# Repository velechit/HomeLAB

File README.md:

# HomeLAB
A miniature electronics lab (Oscilloscope + FuncGen + Breadboard + Arduino) for hobbyists

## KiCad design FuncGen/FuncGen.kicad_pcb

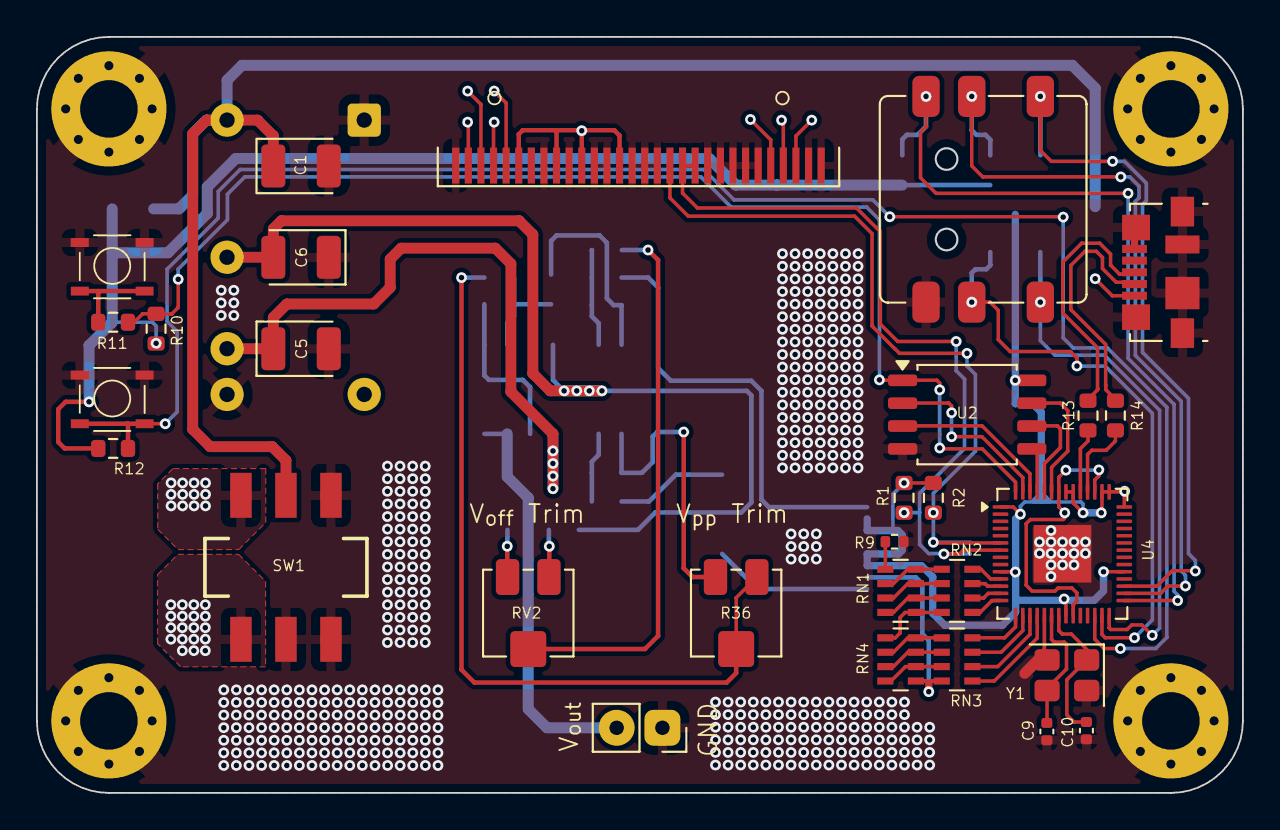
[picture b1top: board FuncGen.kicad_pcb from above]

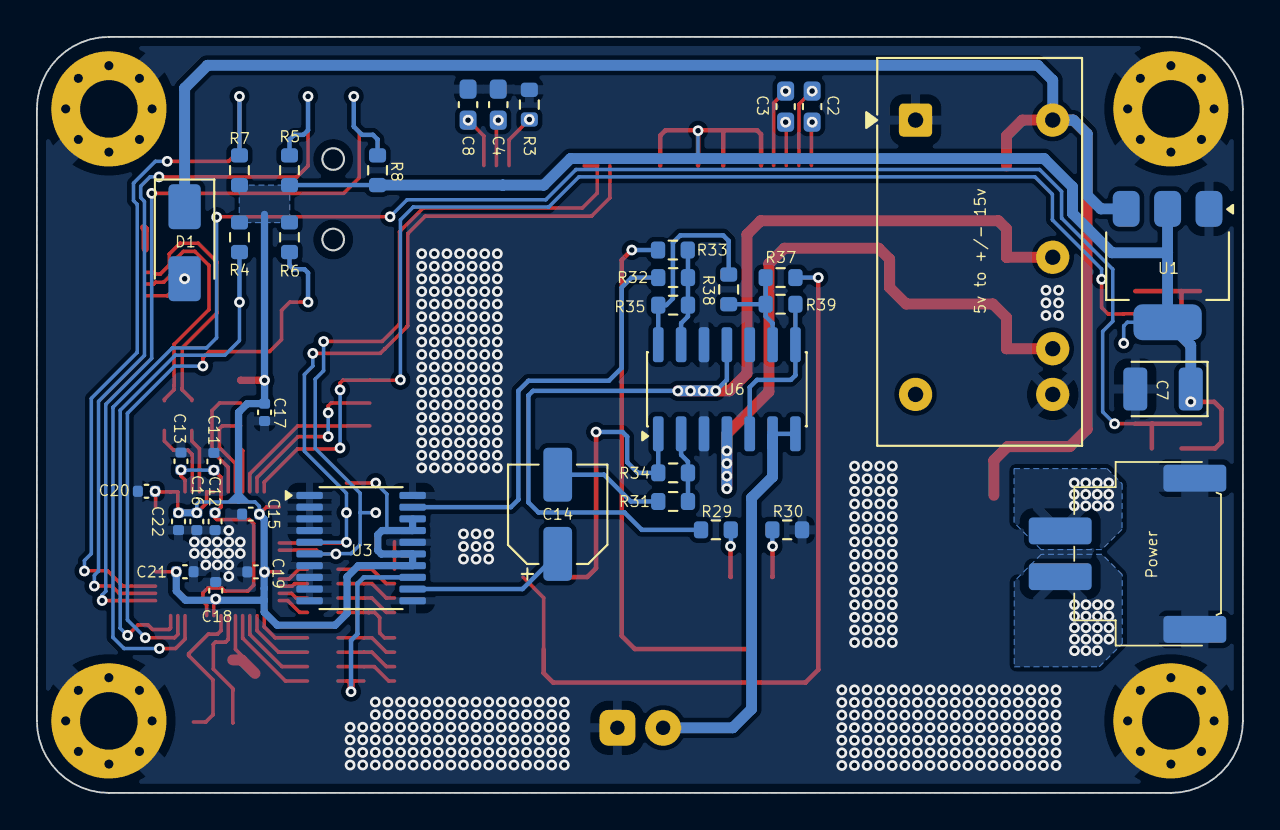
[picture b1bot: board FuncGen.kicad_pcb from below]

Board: 2 copper layers, 67.0 x 42.0 mm, 72 parts (39 on the bottom side), 68 nets.

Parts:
C1: 10u; CP_EIA-3528-21_Kemet-B
C2, C3: 1u; C_0603_1608Metric_Pad1.08x0.95mm_HandSolder
C4: 4.7u; C_0603_1608Metric_Pad1.08x0.95mm_HandSolder
C5, C6, C7: 4.7u; CP_EIA-3528-21_Kemet-B
C8: 2.2u; C_0603_1608Metric_Pad1.08x0.95mm_HandSolder
C9, C10: 22p; C_0402_1005Metric
C11, C12, C15, C16, C17, C18, C19, C20, C21: 100n; C_0402_1005Metric
C13, C22: 1u; C_0402_1005Metric
C14: 47u; CP_Elec_5x5.4
D1: SS34; D_SMA
DS1: 0.96" 128x64 OLED; OLED-128O064D
H1, H2, H3, H4: MountingHole_Pad; MountingHole_3.2mm_M3_Pad_Via
J1: PWR; batt-conn
J2: joystick-sleek
J3: USB_B_Micro; USB_Micro-B_Molex_47346-0001
J4: Conn_01x02; PinSocket_1x02_P2.54mm_Vertical
PS1: IA0515D; Converter_DCDC_XP_POWER-IAxxxxD_THT
R1, R2: 3.3k; R_0603_1608Metric
R3: 910k; R_0603_1608Metric
R4, R5, R6, R7, R8, R10, R12, R31: 10k; R_0603_1608Metric
R9: 10k; R_0402_1005Metric
R11, R30: 1k; R_0603_1608Metric
R13, R14: 27; R_0603_1608Metric
R29: 22k; R_0603_1608Metric
R32, R33, R38, R39: 100k; R_0603_1608Metric
R34, R37: 27k; R_0603_1608Metric
R35: 470k; R_0603_1608Metric
R36: 5k; Potentiometer_Bourns_3224J_Horizontal
RN1, RN4: 10k; R_Array_Concave_4x0603
RN2, RN3: 20k; R_Array_Concave_4x0603
RV2: 5k; Potentiometer_Bourns_3224J_Horizontal
SW1: PWR_SW; DPDT_SMT
SW2: BOOT; 4PINSW-MINI
SW3: RESET; 4PINSW-MINI
U1: LM1117; SOT-223-3_TabPin2
U2: W25Q32JVSS; SOIC-8_5.3x5.3mm_P1.27mm
U3: MCP4461-103; TSSOP-20_4.4x6.5mm_P0.65mm
U4: RP2040; QFN-56-1EP_7x7mm_P0.4mm_EP3.2x3.2mm
U6: TL074; SOIC-14_3.9x8.7mm_P1.27mm
Y1: 12MHz; Crystal_SMD_3225-4Pin_3.2x2.5mm

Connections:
+1V1: C11.2, C12.2, C13.2, U4.23 (DVDD), U4.45 (VREG_VOUT), U4.50 (DVDD)
+3V3: C7.1, C15.2, C16.2, C17.2, C18.2, C19.2, C20.2, C21.2, C22.2, DS1.6 (VBAT), DS1.9 (VDD), DS1.11 (BS1), DS1.14 (~RES), R1.1, R2.1, R4.1, R5.1, R6.1, R7.1, R8.1, R10.1, R12.1, U1.2 (VO), U2.8 (VCC), U3.14 (~WP), U3.15 (~RESET), U3.17 (VDD), U3.18 (P2B), U4.1 (IOVDD), U4.10 (IOVDD), U4.22 (IOVDD), U4.33 (IOVDD), U4.42 (IOVDD), U4.43 (ADC_AVDD), U4.44 (VREG_IN), U4.48 (USB_VDD), U4.49 (IOVDD)
+5V: C1.1, D1.1 (K), PS1.3 (+Vin), SW1.5 (B), U1.3 (VI)
+15V: C5.1, PS1.5 (+Vout), U6.4 (V+)
-15V: C6.2, PS1.4 (-Vout), R29.2, U6.11 (V-)
/BTN_DOWN: J2.D, R7.2, U4.31 (GPIO20)
/BTN_LEFT: J2.L, R6.2, U4.27 (GPIO16)
/BTN_MID: J2.M, R4.2, U4.28 (GPIO17)
/BTN_RIGHT: J2.R, R5.2, U4.30 (GPIO19)
/BTN_UP: J2.U, R8.2, U4.29 (GPIO18)
/DAC0: RN2.8 (R1.2), U4.11 (GPIO8)
/DAC1: RN2.7 (R2.2), U4.12 (GPIO9)
/DAC2: RN2.6 (R3.2), U4.13 (GPIO10)
/DAC3: RN2.5 (R4.2), U4.14 (GPIO11)
/DAC4: RN3.8 (R1.2), U4.15 (GPIO12)
/DAC5: RN3.7 (R2.2), U4.16 (GPIO13)
/DAC6: RN3.6 (R3.2), U4.17 (GPIO14)
/DAC7: RN3.5 (R4.2), U4.18 (GPIO15)
/QSPI_CLK: U2.6 (CLK), U4.52 (QSPI_SCLK)
/QSPI_SD0: U2.5 (DI/IO_{0}), U4.53 (QSPI_SD0)
/QSPI_SD1: U2.2 (DO/IO_{1}), U4.55 (QSPI_SD1)
/QSPI_SD2: U2.3 (~WP/IO_{2}), U4.54 (QSPI_SD2)
/QSPI_SD3: U2.7 (~HOLD/~RESET/IO_{3}), U4.51 (QSPI_SD3)
/QSPI_SS: R10.2, R11.1, U2.1 (~CS), U4.56 (QSPI_SS)
/SCL: DS1.18 (D0), R2.2, U3.5 (SCL), U4.6 (GPIO4)
/SDA: DS1.19 (D1), DS1.20 (D2), R1.2, U3.6 (SDA), U4.7 (GPIO5)
/USB.D+: J3.3 (D+), R13.1
/USB.D-: J3.2 (D-), R14.1
GND: C1.2, C4.1, C5.2, C6.1, C7.2, C8.1, C9.1, C10.1, C11.1, C12.1, C13.1, C15.1, C16.1, C17.1, C18.1, C19.1, C20.1, C21.1, C22.1, DS1.1 (GND), DS1.8 (VSS), DS1.10 (BS0), DS1.12 (BS2), DS1.13 (~CS), DS1.15 (D/~C), DS1.16 (R/~W), DS1.17 (E/~RD), DS1.21 (D3), DS1.22 (D4), DS1.23 (D5), DS1.24 (D6), DS1.25 (D7), DS1.29 (VLSS), DS1.30 (GND), H1.1, H2.1, H3.1, H4.1, J1.3, J2.COM, J3.5 (GND), J3.6 (Shield), J4.1, PS1.1 (-Vin), PS1.6 (0V), R3.2, R9.2, R30.1, SW1.2 (B), SW1.3 (C), SW1.4 (A), SW2.1, SW3.1, U1.1 (GND), U2.4 (GND), U3.1 (P3A), U3.2 (P3W), U3.3 (P3B), U3.4 (HVC/A0), U3.7 (VSS), U3.8 (P1B), U3.9 (P1W), U3.10 (P1A), U3.11 (P0A), U3.16 (A1), U3.20 (P2A), U4.19 (TESTEN), U4.57 (GND), U6.3 (+), U6.10 (+), U6.12 (+), Y1.2, Y1.4
GNDS: J1.1, SW1.1 (A)
unnamed: C14.2, R31.1
unnamed: D1.2 (A), J3.1 (VBUS)
unnamed: C3.2, DS1.5 (C1N)
unnamed: C3.1, DS1.4 (C1P)
unnamed: C2.1, DS1.2 (C2N)
unnamed: C2.2, DS1.3 (C2P)
unnamed: DS1.26 (IREF), R3.1
unnamed: C8.2, DS1.28 (VCC)
unnamed: C4.2, DS1.27 (VCOMH)
unnamed: R11.2, SW2.2
unnamed: R29.1, RV2.3
unnamed: R30.2, RV2.1
unnamed: R33.1, RV2.2
unnamed: R34.2, R36.1, U6.1
unnamed: R35.2, R38.1, U6.14
unnamed: R36.2, R36.3, R37.1
unnamed: R9.1, RN1.1 (R1.1)
unnamed: RN1.2 (R2.1), RN1.8 (R1.2), RN2.1 (R1.1)
unnamed: RN1.3 (R3.1), RN1.7 (R2.2), RN2.2 (R2.1)
unnamed: RN1.4 (R4.1), RN1.6 (R3.2), RN2.3 (R3.1)
unnamed: RN1.5 (R4.2), RN2.4 (R4.1), RN4.1 (R1.1)
unnamed: RN3.1 (R1.1), RN4.2 (R2.1), RN4.8 (R1.2)
unnamed: RN3.2 (R2.1), RN4.3 (R3.1), RN4.7 (R2.2)
unnamed: RN3.3 (R3.1), RN4.4 (R4.1), RN4.6 (R3.2)
unnamed: C14.1, U3.12 (P0W)
unnamed: R32.1, U3.19 (P2W)
unnamed: R12.2, SW3.2, U4.26 (RUN)
unnamed: R14.2, U4.46 (USB_DM)
unnamed: R13.2, U4.47 (USB_DP)
unnamed: C9.2, U4.20 (XIN), Y1.3
unnamed: C10.2, U4.21 (XOUT), Y1.1
unnamed: R31.2, R34.1, U6.2 (-)
unnamed: R39.2, U6.5 (+), U6.8
unnamed: R37.2, R38.2, R39.1, U6.9 (-)
unnamed: R32.2, R33.2, R35.1, U6.13 (-)
VDD: J1.2, SW1.6 (C)
VOUT: J4.2, U6.6 (-), U6.7
Vsig: RN3.4 (R4.1), RN4.5 (R4.2), U3.13 (P0B)

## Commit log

2025-10-31 Initial commit for Function Gemerator PCB
2025-10-31 Cleanup
2025-10-31 Placeholder for Oscilloscope board design
2025-10-31 Place holder for Function Generator Firmware
